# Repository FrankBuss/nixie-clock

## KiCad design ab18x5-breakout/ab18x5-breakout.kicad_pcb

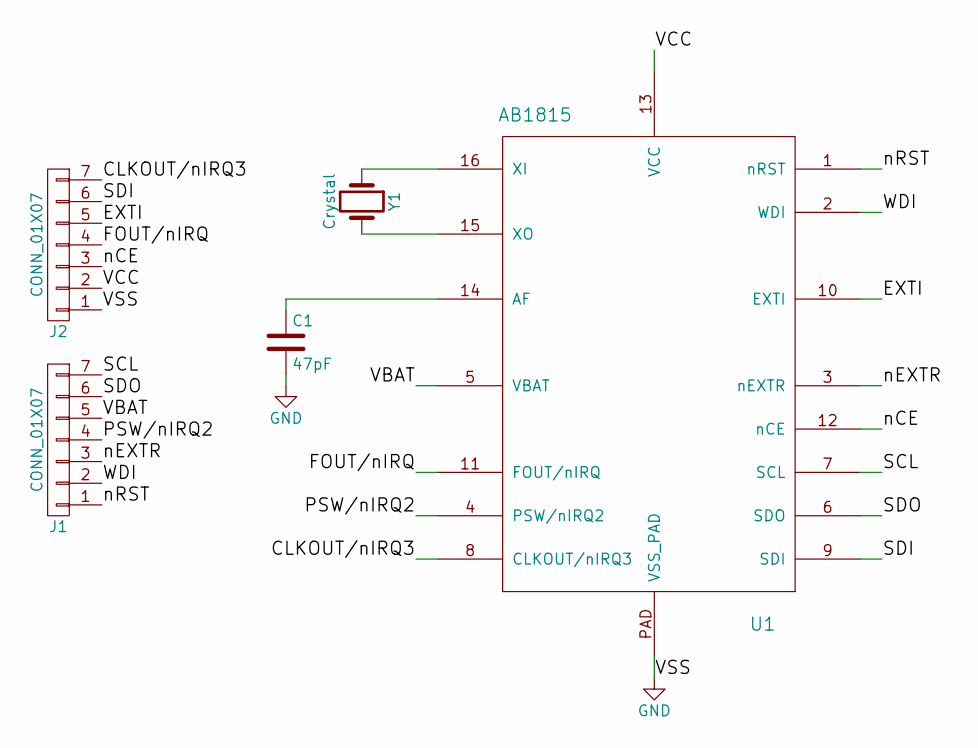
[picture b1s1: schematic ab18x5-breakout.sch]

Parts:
C1: 47pF; C_0603_HandSoldering
J1, J2: CONN_01X07; Pin_Header_Straight_1x07_Pitch2.54mm
U1: AB1815; qfn16
Y1: Crystal; crystal

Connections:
/CLKOUT/nIRQ3: J2.7, U1.8 (CLKOUT/nIRQ3)
/EXTI: J2.5, U1.10 (EXTI)
/FOUT/nIRQ: J2.4, U1.11 (FOUT/nIRQ)
/PSW/nIRQ2: J1.4, U1.4 (PSW/nIRQ2)
/SCL: J1.7, U1.7 (SCL)
/SDI: J2.6, U1.9 (SDI)
/SDO: J1.6, U1.6 (SDO)
/VBAT: J1.5, U1.5 (VBAT)
/VCC: J2.2, U1.13 (VCC)
/WDI: J1.2, U1.2 (WDI)
/nCE: J2.3, U1.12 (nCE)
/nEXTR: J1.3, U1.3 (nEXTR)
/nRST: J1.1, U1.1 (nRST)
GND: C1.2, J2.1, U1.PAD (VSS_PAD)
unnamed: C1.1, U1.14 (AF)
unnamed: U1.15 (XO), Y1.2
unnamed: U1.16 (XI), Y1.1

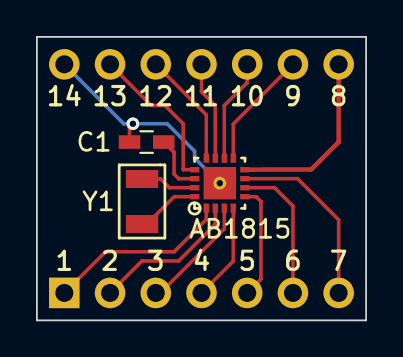
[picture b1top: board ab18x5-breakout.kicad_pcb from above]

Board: 2 copper layers, 18.3 x 15.7 mm, 5 parts (0 on the bottom side), 17 nets.

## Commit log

2017-04-07 make ModelSim happy
2017-04-21 breakout board for the AB1815 RTC chip
2017-04-22 adding 3D models and better silk screen
